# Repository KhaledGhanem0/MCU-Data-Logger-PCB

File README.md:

# MCU Data Logger PCB

A compact, battery-powered data logger PCB built around the **ATmega328P**, designed in KiCad. The board integrates an RTC for timestamping and dual EEPROM chips for storage, with all peripherals communicating over I2C. The design was optimized from an initial 4-layer layout down to 2 layers, cutting manufacturing cost from ~$8 to ~$2 per piece without sacrificing functionality.

---

## Table of Contents

- [Overview](#overview)
- [Schematic](#schematic)
- [PCB Layout](#pcb-layout)
- [3D Render](#3d-render)
- [Design Optimization](#design-optimization)
- [Design Specifications](#design-specifications)
- [Bill of Materials](#bill-of-materials)
- [File Structure](#file-structure)
- [License](#license)

---

## Overview

The board is designed to log data autonomously using an ATmega328P microcontroller. A DS1337S real-time clock provides accurate timestamps via I2C, and two 24LC1025 EEPROM chips (totaling 256 KB of storage) hold the logged data on the same bus. The entire system runs off a battery, with decoupling capacitors stabilizing the supply at the MCU.

External connectivity is handled through a dedicated connectors sheet (sheet 2 of the schematic), which breaks out I2C, UART, GPIO, and ICSP headers — allowing the board to interface with sensors or be reprogrammed in-circuit without any additional hardware.

The key engineering challenge of this project was reducing the board from 4 layers to 2 while keeping all signals properly routed in a compact 50.8 × 30.5 mm footprint.

---

## Schematic

The schematic is split across two sheets. Sheet 1 captures the full circuit — MCU, RTC, EEPROM, power, and passive components. Sheet 2 is an embedded sub-sheet dedicated to the external connectors, keeping the top-level diagram uncluttered.

**Sheet 1 — Main Circuit**

**Sheet 2 — Connectors**

Key connections documented in the schematic:

- **ATmega328P (U4)** — main MCU with a 16 MHz external crystal (Y2) and a 10k reset pull-up (R6)
- **DS1337S RTC (U2)** — I2C real-time clock with a 32.768 kHz crystal (Y1) and 10k I2C pull-ups (R1, R2)
- **24LC1025 EEPROM × 2 (U1, U3)** — dual EEPROM chips on the I2C bus with 4.7k pull-ups (R3, R4)
- **Battery (BT1)** — sole power source for the board
- **Status LED (D1, D2)** — with 330 Ω current-limiting resistors (R5, R7)
- **Connectors (Sheet 2)** — I2C header (J1), Serial UART header (J3), GPIO header (J2, 7 digital pins), ICSP header (J4)

## PCB Layout

All 29 components are placed on the front side of the board. The back copper layer (B.Cu) is used as a ground pour, with signal and power routing handled on the front. Power traces run at 0.35 mm and signal traces at 0.2 mm throughout.

Routing highlights:

- **39 through vias** used to transition between layers and connect to the ground pour
- **Ground copper pour** applied to B.Cu, stitched to the GND net
- **Power netclass** (Vcc, GND): 0.35 mm trace width, 0.8 mm via diameter
- **Default netclass** (signals): 0.2 mm trace width, 0.6 mm via diameter, 0.3 mm drill

## 3D Render

---

## Design Optimization

The most significant design decision in this project was reducing the layer count from 4 to 2.

The initial 4-layer stackup was used to handle signal routing and grounding cleanly, with dedicated inner layers for power and ground planes. While functional, a 4-layer board costs roughly 4× more to manufacture than a 2-layer board at low quantities (~$8 vs ~$2 per piece).

To bring it down to 2 layers, the routing strategy was reworked: signals were rerouted to avoid conflicts without relying on inner layers, the ground plane was moved to B.Cu as a copper pour, and via placement was adjusted to maintain connectivity. The result is a board that meets the same electrical requirements at a fraction of the cost — a meaningful difference at any prototype or small-batch quantity.

## Design Specifications

### Board Stackup

| Layer | Type | Thickness | Material |
|---|---|---|---|
| F.Silkscreen | Top Silk Screen | — | — |
| F.Mask | Top Solder Mask | 0.01 mm | Epsilon R: 3.3 |
| F.Cu | Copper | 0.035 mm | — |
| Dielectric 1 | Core | 1.51 mm | FR4 |
| B.Cu | Copper | 0.035 mm | — |
| B.Mask | Bottom Solder Mask | 0.01 mm | Epsilon R: 3.3 |

**Total board thickness:** 1.6 mm | **Solder mask color:** Green

### Board Dimensions

| Property | Value |
|---|---|
| Width | 50.800 mm |
| Height | 30.480 mm |
| Area | 1,548.4 mm² |

### Routing Rules

| Parameter | Power Net | Default Net |
|---|---|---|
| Clearance | 0.25 mm | 0.20 mm |
| Trace width | 0.35 mm | 0.20 mm |
| Via diameter | 0.80 mm | 0.60 mm |
| Via drill | — | 0.30 mm |

### Board Statistics

| Item | Count |
|---|---|
| Total components | 29 |
| SMD components | 20 |
| THT components | 5 |
| Through vias | 39 |
| SMD pads | 88 |
| Through-hole pads | 25 |
| Mounting holes (NPTH) | 4 |

## Bill of Materials

| Reference | Description | Value | Qty |
|---|---|---|---|
| U4 | Microcontroller, TQFP-32 | ATmega328P-AU | 1 |
| U2 | Real-time clock, SOIC-8 | DS1337S | 1 |
| U1, U3 | EEPROM 1 Mbit, I2C, SOIC-8 | 24LC1025 | 2 |
| Y2 | Crystal oscillator | 16 MHz | 1 |
| Y1 | Crystal oscillator | 32.768 kHz | 1 |
| BT1 | Battery holder | — | 1 |
| D1, D2 | LED, 5 mm | — | 2 |
| R1, R2 | Resistor, I2C pull-up (RTC) | 10k Ω | 2 |
| R3, R4 | Resistor, I2C pull-up (EEPROM) | 4.7k Ω | 2 |
| R5, R7 | Resistor, LED current-limiting | 330 Ω | 2 |
| R6 | Resistor, reset pull-up | 10k Ω | 1 |
| C1, C4 | Decoupling capacitor | 0.1 µF | 2 |
| C2, C3 | Crystal load capacitor | 22 pF | 2 |
| C5 | Decoupling capacitor | 100 nF | 1 |
| J1 | I2C header | Conn_01×04_Pin | 1 |
| J2 | GPIO header | Conn_01×09_Pin | 1 |
| J3 | Serial UART header | Conn_01×04_Pin | 1 |
| J4 | ICSP header | Conn_02×03_Odd_Even | 1 |
| H1–H4 | Mounting holes | — | 4 |

---

## File Structure

```
├── kicad/
│   ├── MCU_Datalogger.kicad_pro        # KiCad project file
│   ├── MCU_Datalogger.kicad_sch        # Main schematic (sheet 1)
│   ├── Connectors.kicad_sch            # Connectors sub-sheet (sheet 2)
│   ├── MCU_Datalogger.kicad_pcb        # PCB layout
│   └── fp-lib-table                    # Footprint library references
├── assets/
│   ├── schematic_main.pdf              # Schematic sheet 1 export
│   ├── schematic_connectors.pdf        # Schematic sheet 2 export
│   ├── pcb_layout.png                  # PCB layout screenshot
│   ├── 3d_front.png                    # 3D render, front side
│   └── 3d_back.png                     # 3D render, back side
├── LICENSE
└── README.md
```

---

## License

This project is licensed under the [MIT License](LICENSE).

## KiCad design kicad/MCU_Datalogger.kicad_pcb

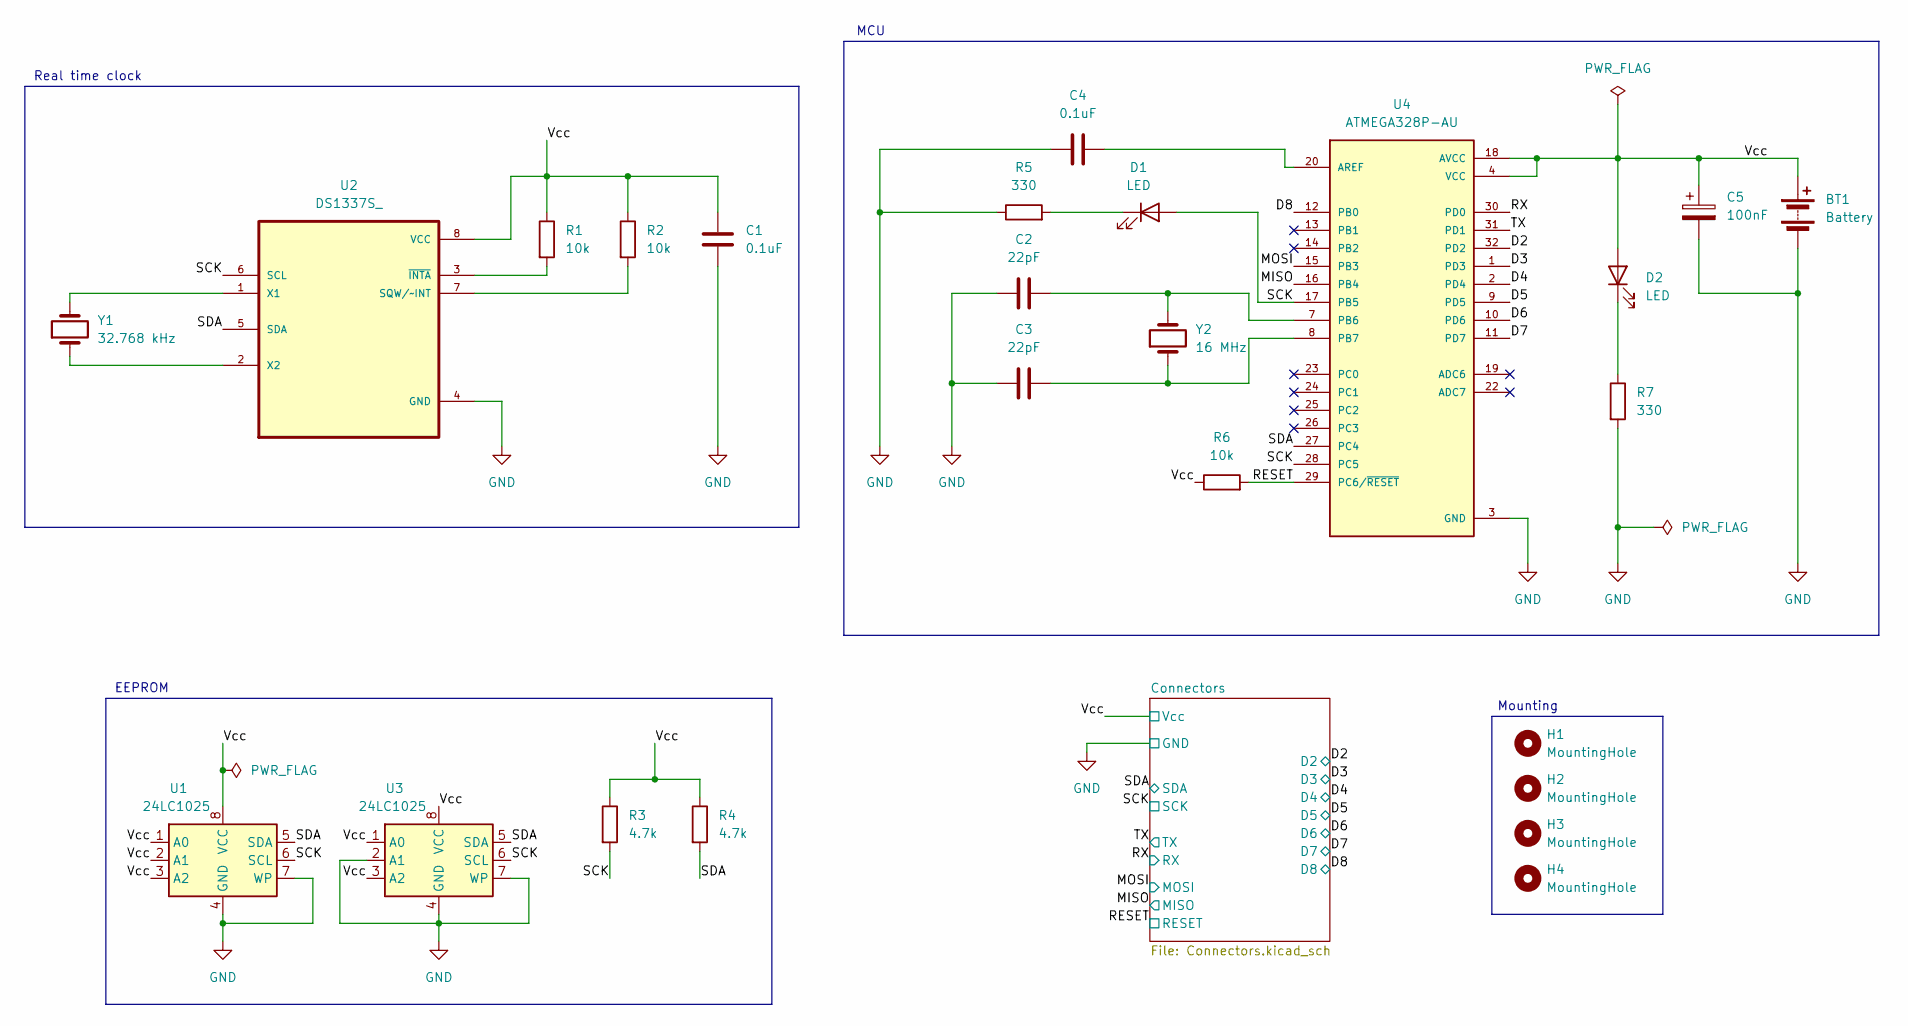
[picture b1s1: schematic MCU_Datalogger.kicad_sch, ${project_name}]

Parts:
BT1: Battery; PinHeader_1x02_P2.54mm_Vertical
C1, C4: 0.1uF; C_0805_2012Metric
C2, C3: 22pF; C_0805_2012Metric
C5: 100nF; C_0805_2012Metric
D1, D2: LED; LED_0805_2012Metric
H1, H2, H3, H4: MountingHole; MountingHole_2.1mm
R1, R2, R6: 10k; R_0805_2012Metric
R3, R4: 4.7k; R_0805_2012Metric
R5, R7: 330; R_0805_2012Metric
U1, U3: 24LC1025; SOIC-8_5.3x5.3mm_P1.27mm
U2: DS1337S_; SOIC127P600X175-8N
U4: ATMEGA328P-AU; QFP80P900X900X120-32N; PARTREV 8271A; DigiKey_Part_Number ATMEGA328P-AU-ND
Y1: 32.768 kHz; Crystal_SMD_5032-2Pin_5.0x3.2mm_HandSoldering
Y2: 16 MHz; Crystal_SMD_5032-2Pin_5.0x3.2mm_HandSoldering

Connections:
/D2: U4.32 (PD2); also elsewhere on the board
/D3: U4.1 (PD3); also elsewhere on the board
/D4: U4.2 (PD4); also elsewhere on the board
/D5: U4.9 (PD5); also elsewhere on the board
/D6: U4.10 (PD6); also elsewhere on the board
/D7: U4.11 (PD7); also elsewhere on the board
/D8: U4.12 (PB0); also elsewhere on the board
/MISO: U4.16 (PB4); also elsewhere on the board
/MOSI: U4.15 (PB3); also elsewhere on the board
/RESET: R6.2, U4.29 (PC6/~RESET); also elsewhere on the board
/RX: U4.30 (PD0); also elsewhere on the board
/SCK: D1.2 (A), R3.2, U1.6 (SCL), U2.6 (SCL), U3.6 (SCL), U4.17 (PB5), U4.28 (PC5); also elsewhere on the board
/SDA: R4.2, U1.5 (SDA), U2.5 (SDA), U3.5 (SDA), U4.27 (PC4); also elsewhere on the board
/TX: U4.31 (PD1); also elsewhere on the board
GND: BT1.2 (-), C1.2, C2.1, C3.1, C4.1, C5.2, R5.1, R7.2, U1.4 (GND), U1.7 (WP), U2.4 (GND), U3.2 (A1), U3.4 (GND), U3.7 (WP), U4.3 (GND), U4.5 (GND), U4.21 (GND); also elsewhere on the board
unnamed: D1.1 (K), R5.2
unnamed: D2.1 (K), R7.1
unnamed: R2.2, U2.7 (SQW/~INT)
unnamed: U2.1 (X1), Y1.2
unnamed: U2.2 (X2), Y1.1
unnamed: R1.2, U2.3 (~INTA)
unnamed: C4.2, U4.20 (AREF)
unnamed: C2.2, U4.7 (PB6), Y2.2
unnamed: C3.2, U4.8 (PB7), Y2.1
VCC: BT1.1 (+), C1.1, C5.1, D2.2 (A), R1.1, R2.1, R3.1, R4.1, R6.1, U1.1 (A0), U1.2 (A1), U1.3 (A2), U1.8 (VCC), U2.8 (VCC), U3.1 (A0), U3.3 (A2), U3.8 (VCC), U4.4 (VCC), U4.6 (VCC), U4.18 (AVCC); also elsewhere on the board

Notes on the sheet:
Real time clock
Mounting
MCU
EEPROM

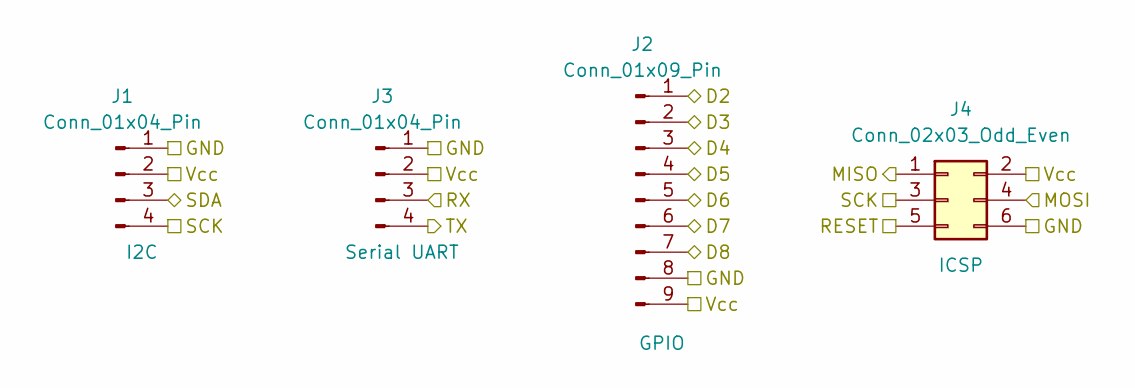
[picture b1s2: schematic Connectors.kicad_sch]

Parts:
J1, J3: Conn_01x04_Pin; PinHeader_1x04_P2.54mm_Vertical
J2: Conn_01x09_Pin; PinHeader_1x09_P2.54mm_Vertical
J4: Conn_02x03_Odd_Even; PinHeader_2x03_P2.54mm_Vertical

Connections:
/D2: J2.1; also elsewhere on the board
/D3: J2.2; also elsewhere on the board
/D4: J2.3; also elsewhere on the board
/D5: J2.4; also elsewhere on the board
/D6: J2.5; also elsewhere on the board
/D7: J2.6; also elsewhere on the board
/D8: J2.7; also elsewhere on the board
/MISO: J4.1; also elsewhere on the board
/MOSI: J4.4; also elsewhere on the board
/RESET: J4.5; also elsewhere on the board
/RX: J3.3; also elsewhere on the board
/SCK: J1.4, J4.3; also elsewhere on the board
/SDA: J1.3; also elsewhere on the board
/TX: J3.4; also elsewhere on the board
GND: J1.1, J2.8, J3.1, J4.6; also elsewhere on the board
VCC: J1.2, J2.9, J3.2, J4.2; also elsewhere on the board

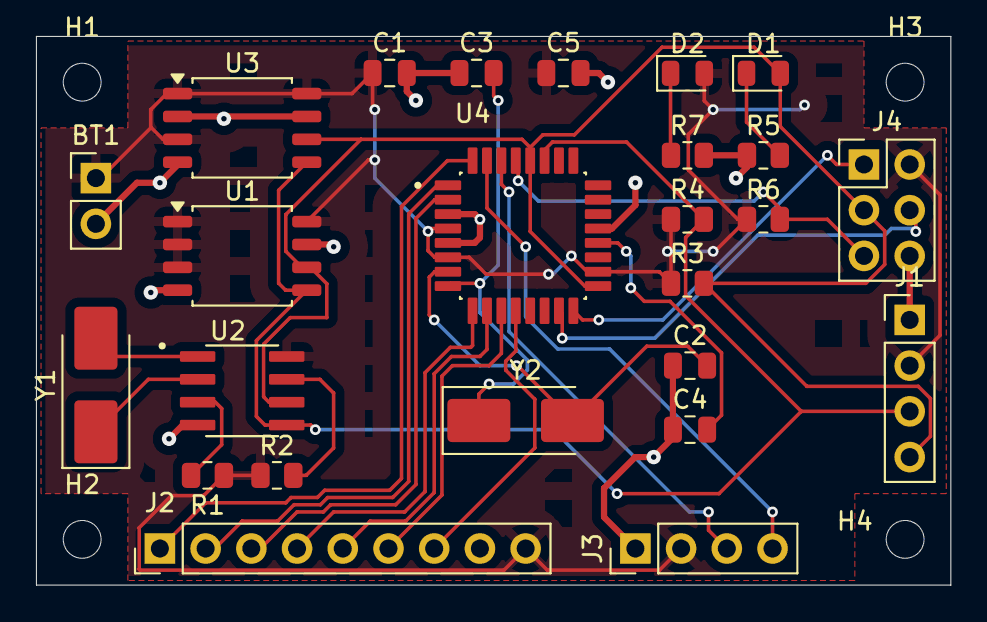
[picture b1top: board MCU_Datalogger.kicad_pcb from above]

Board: 2 copper layers, 50.8 x 30.5 mm, 29 parts (0 on the bottom side), 25 nets.

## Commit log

2026-06-12 Rename schematic_main.pdf to assets/schematic_main.pdf
2026-06-12 Rename Project 3 MCU Datalogger.kicad_pro to kicad/MCU_Datalogger.kicad_pro

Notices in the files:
README.md:
License: MIT
